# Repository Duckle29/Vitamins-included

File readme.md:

View this project on [CADLAB.io](https://cadlab.io/project/1862).   
View the [iBOM](https://duckle29.github.io/Vitamins-included/ibom.html)

# Vitamins Included

This repository contains all files necesarry to make the Let's split keyboard variant "Vitamins included"

Files are not guarranteed to be in sync outside of tagged releases. They aren't on releases either, but they should be ;)

The kit for these PCBs are sold at [Novelkeys](https://novelkeys.xyz), 
the firmware for the keyboard is [QMK](https://github.com/qmk/qmk_firmware/tree/master/keyboards/vitamins_included)

To edit these, you need kicad 5 or later. Missing footprints can be found [here](https://github.com/Duckle29/kicad-footprints), on seperate branches, but should be included in KiCAD libraries eventually. You can check for open pull-requests by me on the upstream repo to see the status on those.

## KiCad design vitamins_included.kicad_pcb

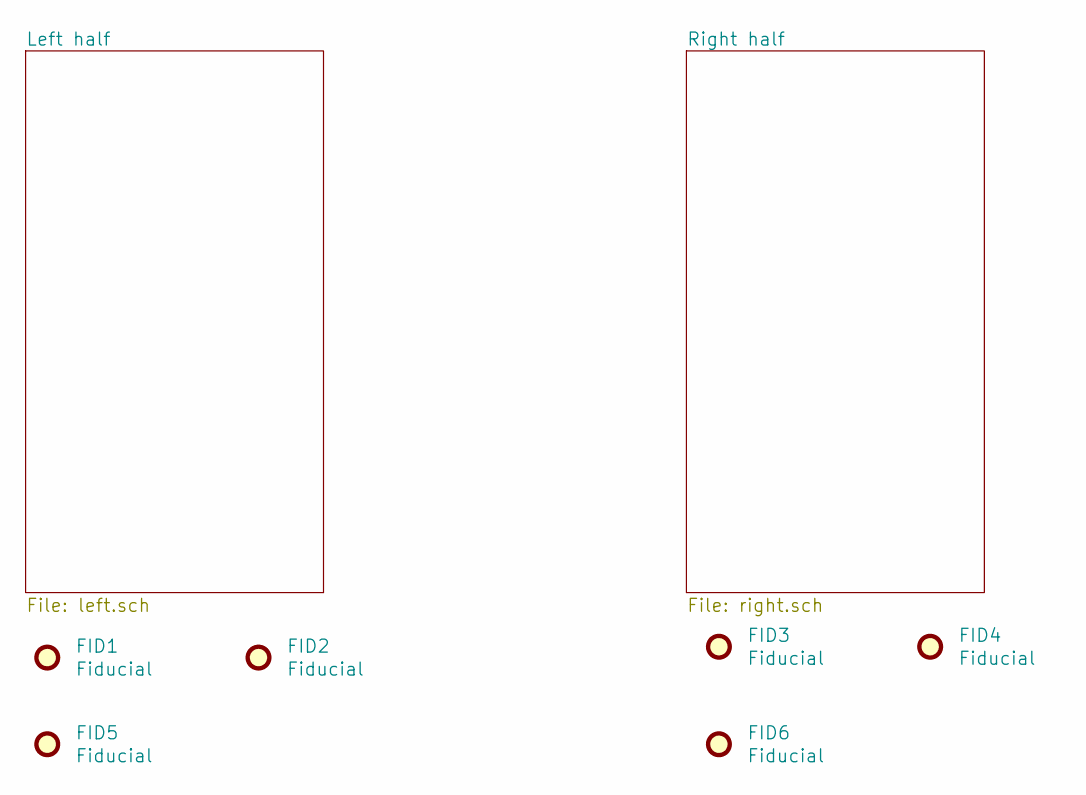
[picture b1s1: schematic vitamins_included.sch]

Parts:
FID1, FID2, FID3, FID4, FID5, FID6: Fiducial; Fiducial_1mm_Dia_2mm_Outer

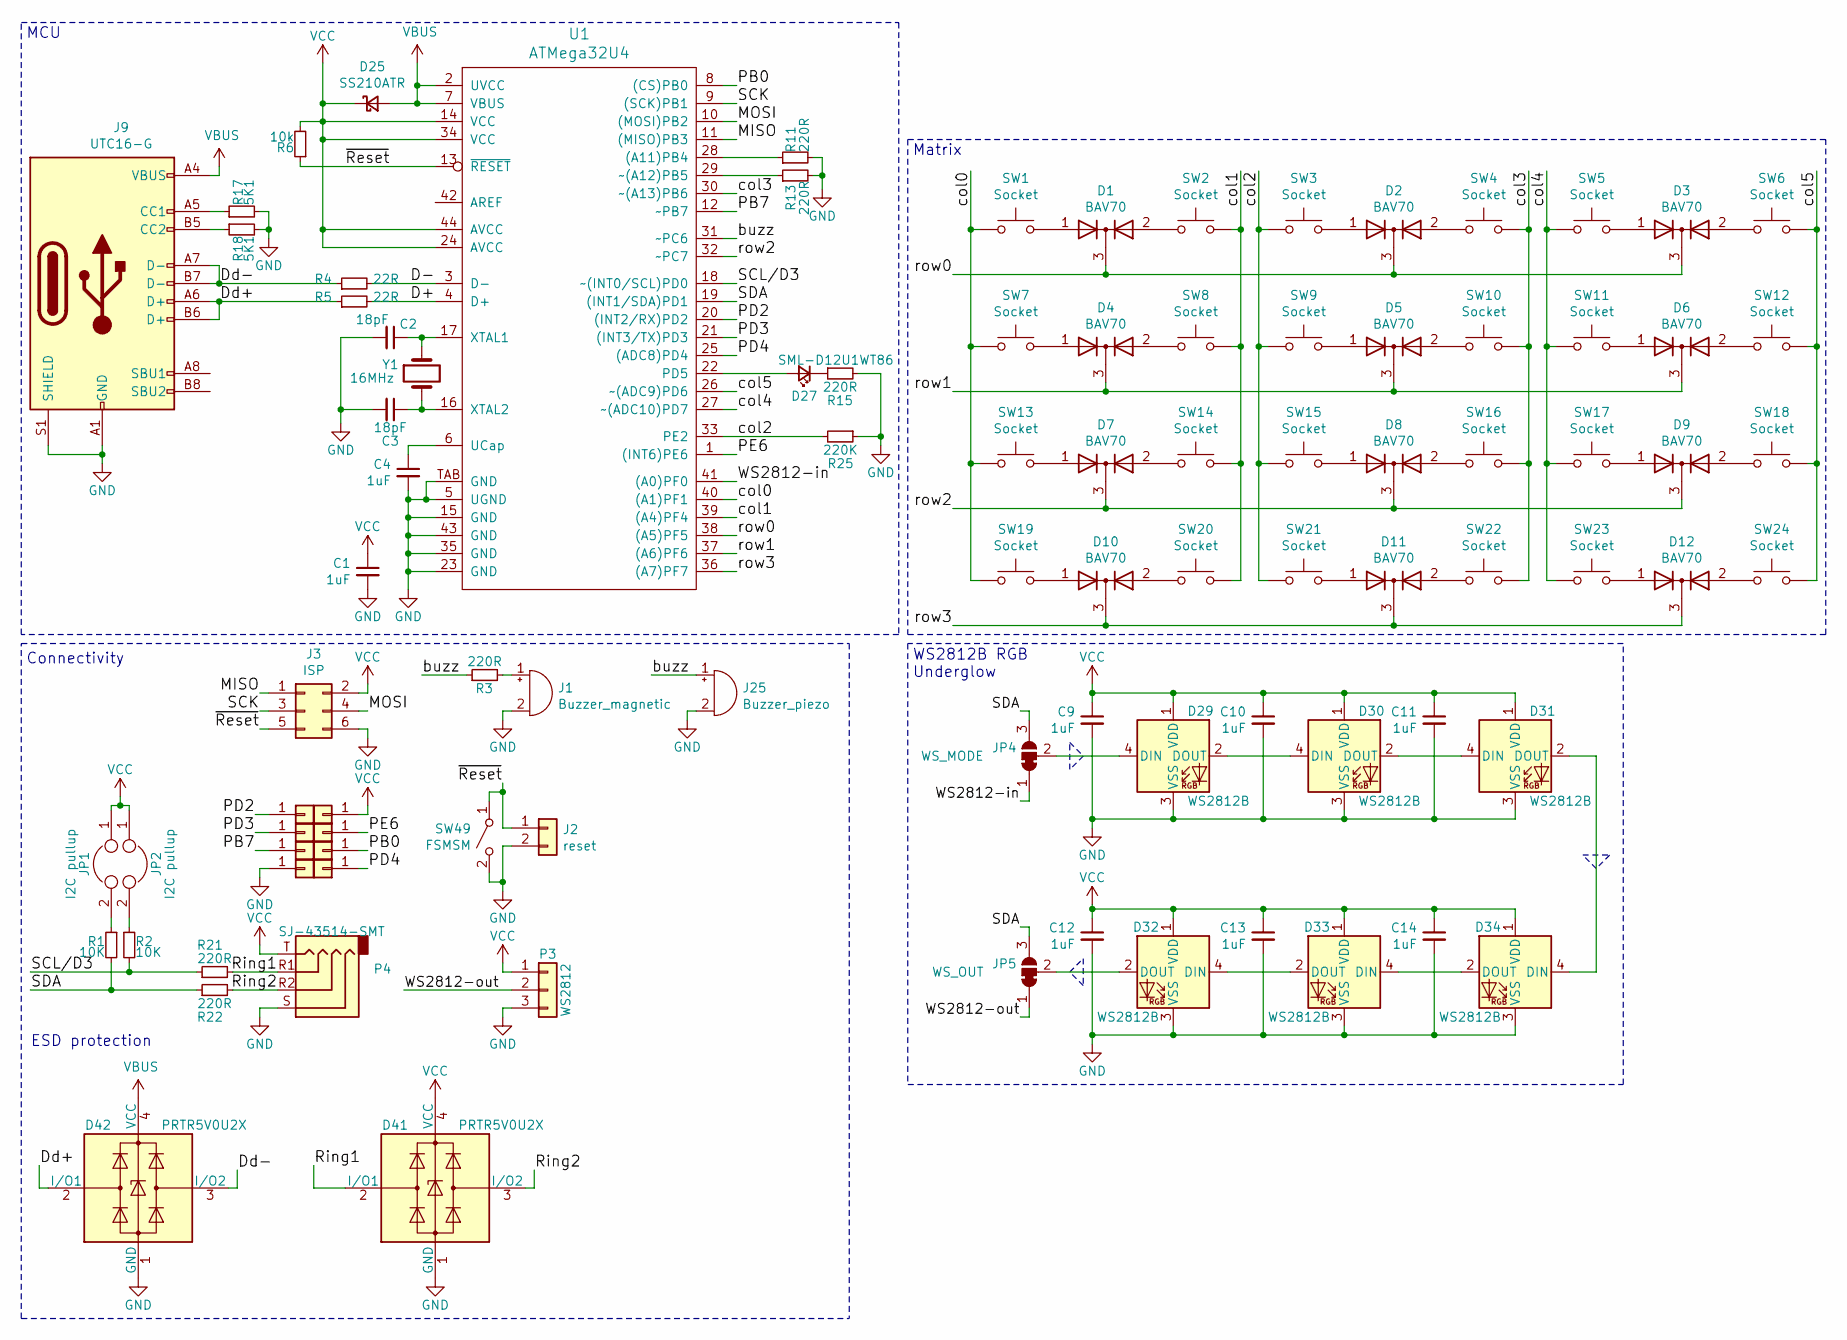
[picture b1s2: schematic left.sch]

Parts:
C1, C4, C9, C10, C11, C12, C13, C14: 1uF; C_0603_1608Metric
C2, C3: 18pF; C_0603_1608Metric
D1, D2, D3, D4, D5, D6, D7, D8, D9, D10, D11, D12: BAV70; SOT-23
D25: SS210ATR; D_SMA
D27: SML-D12U1WT86; LED_0603_1608Metric_Castellated
D29, D30, D31, D32, D33, D34: WS2812B; LED_WS2812B_PLCC4_5.0x5.0mm_P3.2mm
D41, D42: PRTR5V0U2X; SOT-143
J1: Buzzer_magnetic; Buzzer_12x9.5RM7.6
J2: reset; PinHeader_1x02_P2.54mm_Vertical
J3: ISP; Tag-Connect_TC2030-IDC-NL_2x03_P1.27mm_Vertical
J7, J11, J12, J13, J14, J15, J16, J17: Conn_01x01; TestPoint_Pad_D1.5mm
J9: UTC16-G; USB_C_Receptacle_Palconn_UTC16-G
J25: Buzzer_piezo; Buzzer_Mallory_AST1109MLTRQ
JP1, JP2: I2C pullup; Solder-jumper-NO
JP4: WS_MODE; SolderJumper-3_P1.3mm_Bridged12_RoundedPad1.0x1.5mm
JP5: WS_OUT; SolderJumper-3_P1.3mm_Bridged12_RoundedPad1.0x1.5mm
P3: WS2812; SMD_PAD_1x03_Pitch2.54mm
P4: SJ-43514-SMT; SJ-4351X-SMT
R1, R2: 10K; R_0603_1608Metric
R3, R11, R13, R15, R21, R22: 220R; R_0603_1608Metric
R4, R5: 22R; R_0603_1608Metric
R6: 10k; R_0603_1608Metric
R17, R18: 5K1; R_0603_1608Metric
R25: 220K; R_0603_1608Metric
SW1, SW2, SW3, SW4, SW5, SW6, SW7, SW8, SW9, SW10, SW11, SW12, SW13, SW14, SW15, SW16, SW17, SW18, SW19, SW20, SW21, SW22, SW23, SW24: Socket; Kailh-socket
SW49: FSMSM; SW_SPST_FSMSM
U1: ATMega32U4; QFN44G-0.5-7X7MM
Y1: 16MHz; Crystal_SMD_Abracon_ABM3-2pin_5.0x3.2mm

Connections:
/Left half/D+: R5.2, U1.4 (D+)
/Left half/D-: R4.2, U1.3 (D-)
/Left half/Dd+: D42.2 (I/O1), J9.A6 (D+), J9.B6 (D+), R5.1
/Left half/Dd-: D42.3 (I/O2), J9.A7 (D-), J9.B7 (D-), R4.1
/Left half/MISO: J3.1, U1.11 ((MISO)PB3); also elsewhere on the board
/Left half/MOSI: J3.4, U1.10 ((MOSI)PB2); also elsewhere on the board
/Left half/PB0: J15.1, U1.8 ((CS)PB0)
/Left half/PB7: J14.1, U1.12 (~~PB7)
/Left half/PD2: J12.1, U1.20 ((INT2/RX)PD2)
/Left half/PD3: J7.1, U1.21 ((INT3/TX)PD3)
/Left half/PD4: J11.1, U1.25 ((ADC8)PD4)
/Left half/PE6: J13.1, U1.1 ((INT6)PE6)
/Left half/Ring1: D41.2 (I/O1), P4.R1, R21.2
/Left half/Ring2: D41.3 (I/O2), P4.R2, R22.2
/Left half/SCK: J3.3, U1.9 ((SCK)PB1); also elsewhere on the board
/Left half/SCL/D3: R2.2, R21.1, U1.18 (~~(INT0/SCL)PD0)
/Left half/SDA: JP4.3 (B), JP5.3 (B), R1.2, R22.1, U1.19 ((INT1/SDA)PD1)
/Left half/WS2812-in: JP4.1 (A), U1.41 ((A0)PF0)
/Left half/WS2812-out: JP5.1 (A), P3.2
/Left half/buzz: J25.1 (-), R3.1, U1.31 (~~PC6)
/Left half/col0: SW1.1, SW7.1, SW13.1, SW19.1, U1.40 ((A1)PF1)
/Left half/col1: SW2.2, SW8.2, SW14.2, SW20.2, U1.39 ((A4)PF4)
/Left half/col2: R25.2, SW3.1, SW9.1, SW15.1, SW21.1, U1.33 (PE2)
/Left half/col3: SW4.2, SW10.2, SW16.2, SW22.2, U1.30 (~~(A13)PB6)
/Left half/col4: SW5.1, SW11.1, SW17.1, SW23.1, U1.27 (~~(ADC10)PD7)
/Left half/col5: SW6.2, SW12.2, SW18.2, SW24.2, U1.26 (~~(ADC9)PD6); also elsewhere on the board
/Left half/row0: D1.3 (K), D2.3 (K), D3.3 (K), U1.38 ((A5)PF5)
/Left half/row1: D4.3 (K), D5.3 (K), D6.3 (K), U1.37 ((A6)PF6)
/Left half/row2: D7.3 (K), D8.3 (K), D9.3 (K), U1.32 (~~PC7)
/Left half/row3: D10.3 (K), D11.3 (K), D12.3 (K), U1.36 ((A7)PF7)
/Left half/~Reset: J2.1, J3.5, R6.1, SW49.1 (A), U1.13 (~RESET~)
unnamed: C2.1, U1.17 (XTAL1), Y1.1
unnamed: C3.1, U1.16 (XTAL2), Y1.2
unnamed: C4.1, U1.6 (UCap)
unnamed: D1.1 (A), SW1.2
unnamed: D1.2 (A), SW2.1
unnamed: D2.1 (A), SW3.2
unnamed: D2.2 (A), SW4.1
unnamed: D3.1 (A), SW5.2
unnamed: D3.2 (A), SW6.1
unnamed: D4.1 (A), SW7.2
unnamed: D4.2 (A), SW8.1
unnamed: D5.1 (A), SW9.2
unnamed: D5.2 (A), SW10.1
unnamed: D6.1 (A), SW11.2
unnamed: D6.2 (A), SW12.1
unnamed: D7.1 (A), SW13.2
unnamed: D7.2 (A), SW14.1
unnamed: D8.1 (A), SW15.2
unnamed: D8.2 (A), SW16.1
unnamed: D9.1 (A), SW17.2
unnamed: D9.2 (A), SW18.1
unnamed: D10.1 (A), SW19.2
unnamed: D10.2 (A), SW20.1
unnamed: D11.1 (A), SW21.2
unnamed: D11.2 (A), SW22.1
unnamed: D12.1 (A), SW23.2
unnamed 90: D12.2 (A), SW24.1; also elsewhere on the board
unnamed: D27.1 (K), R15.1
unnamed: D27.2 (A), U1.22 (PD5)
unnamed: D29.2 (DOUT), D30.4 (DIN)
unnamed: D29.4 (DIN), JP4.2 (C)
unnamed: D30.2 (DOUT), D31.4 (DIN)
unnamed: D31.2 (DOUT), D34.4 (DIN)
unnamed: D32.2 (DOUT), JP5.2 (C)
unnamed: D32.4 (DIN), D33.2 (DOUT)
unnamed: D33.4 (DIN), D34.2 (DOUT)
unnamed: J1.1 (-), R3.2
unnamed: J9.A5 (CC1), R17.1
unnamed: J9.B5 (CC2), R18.1
unnamed: JP1.2, R1.1
unnamed: JP2.2, R2.1
unnamed: R11.1, U1.28 ((A11)PB4)
unnamed: R13.1, U1.29 (~~(A12)PB5)
VBUS: D25.2 (A), D42.4 (VCC), J9.A4 (VBUS), J9.A9 (VBUS), J9.B4 (VBUS), J9.B9 (VBUS), U1.2 (UVCC), U1.7 (VBUS); also elsewhere on the board
VCC: C1.1, C9.1, C10.1, C11.1, C12.1, C13.1, C14.1, D25.1 (K), D29.1 (VDD), D30.1 (VDD), D31.1 (VDD), D32.1 (VDD), D33.1 (VDD), D34.1 (VDD), D41.4 (VCC), J3.2, J17.1, JP1.1, JP2.1, P3.1, P4.T, R6.2, U1.14 (VCC), U1.24 (AVCC), U1.34 (VCC), U1.44 (AVCC); also elsewhere on the board

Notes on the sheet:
MCU
WS2812B RGB Underglow
Matrix
Connectivity
ESD protection

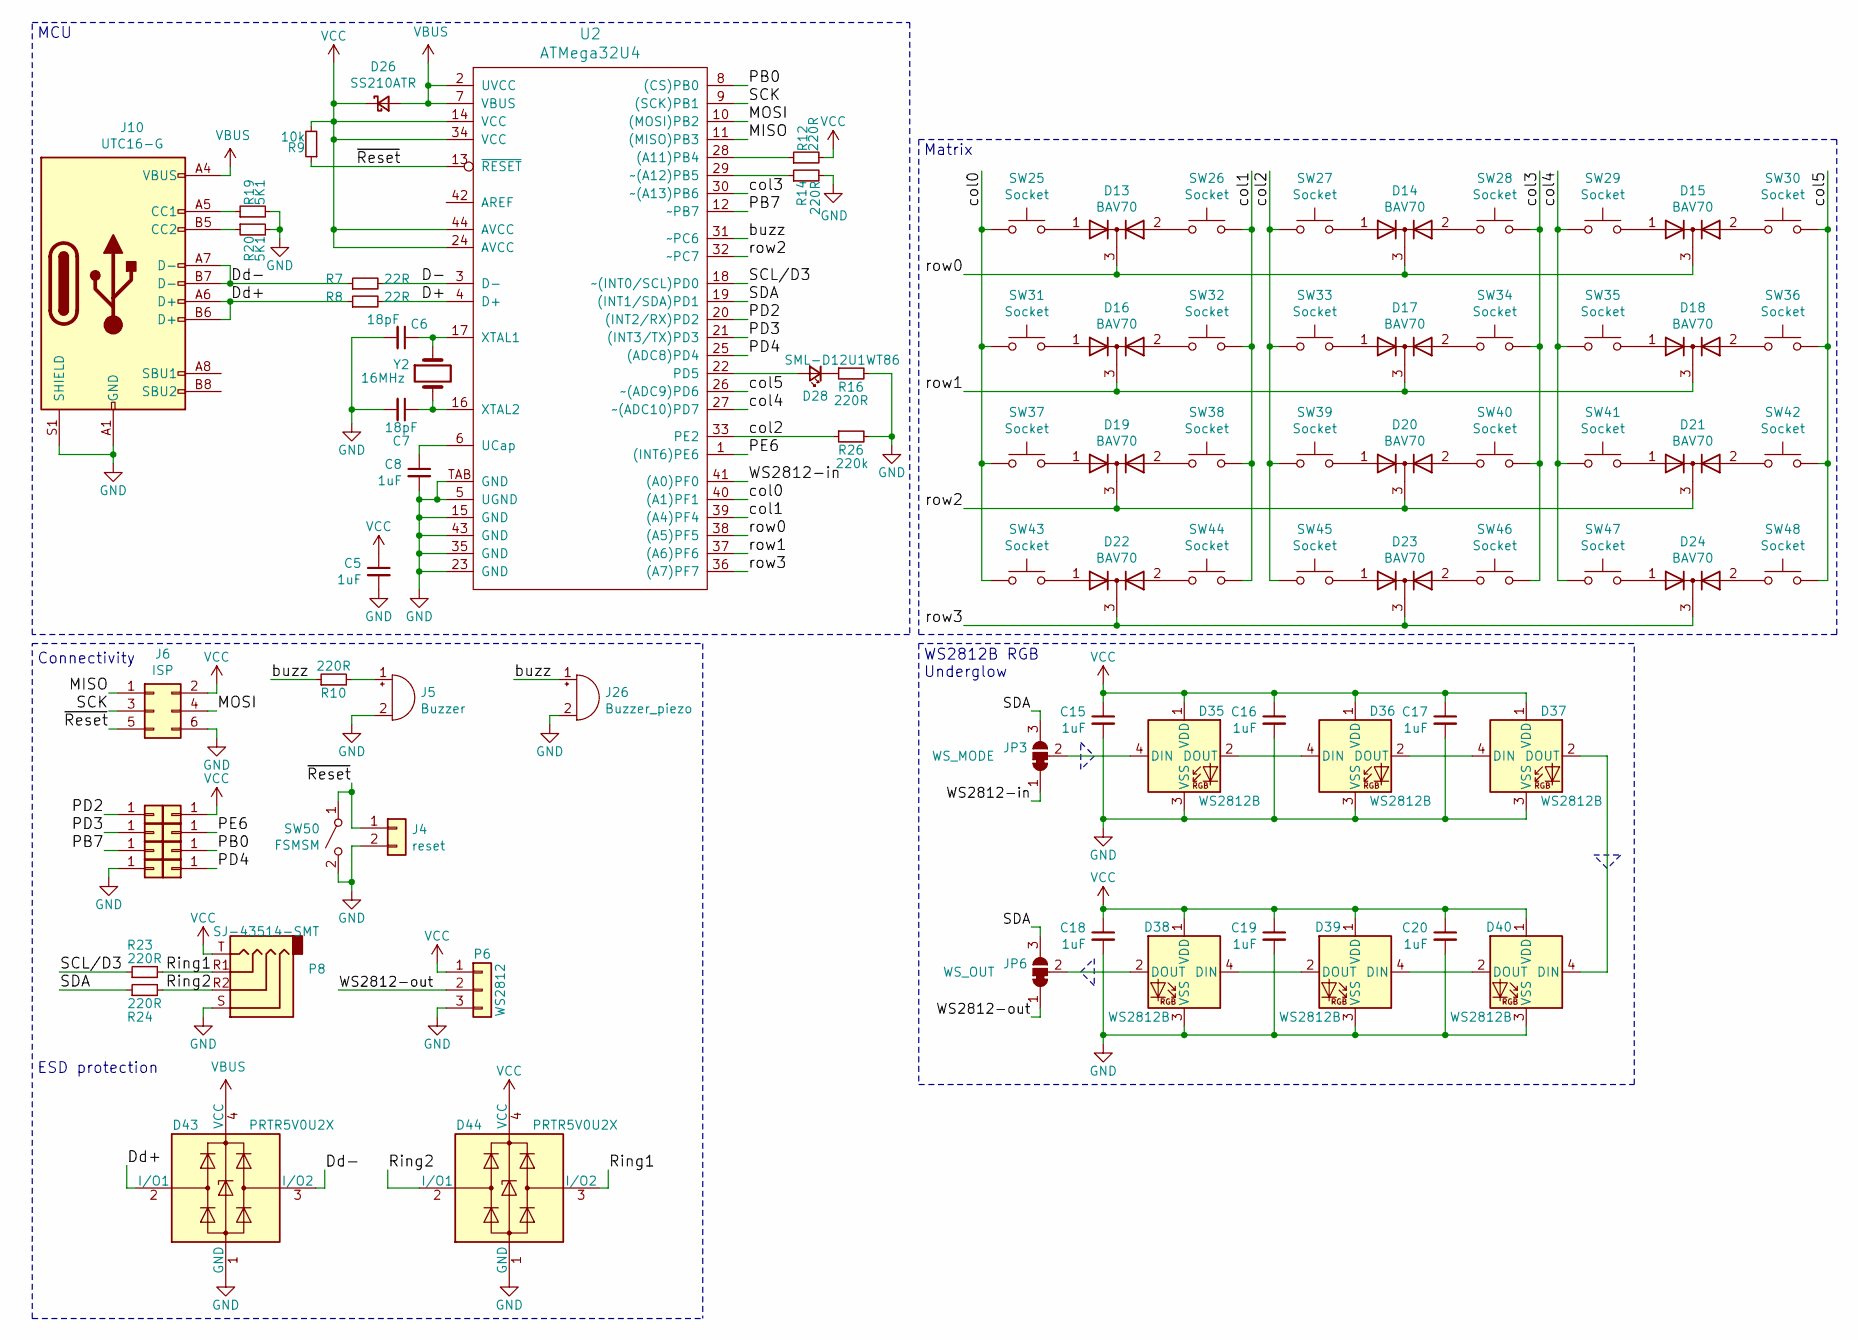
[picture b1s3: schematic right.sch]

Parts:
C5, C8, C15, C16, C17, C18, C19, C20: 1uF; C_0603_1608Metric
C6, C7: 18pF; C_0603_1608Metric
D13, D14, D15, D16, D17, D18, D19, D20, D21, D22, D23, D24: BAV70; SOT-23
D26: SS210ATR; D_SMA
D28: SML-D12U1WT86; LED_0603_1608Metric_Castellated
D35, D36, D37, D38, D39, D40: WS2812B; LED_WS2812B_PLCC4_5.0x5.0mm_P3.2mm
D43, D44: PRTR5V0U2X; SOT-143
J4: reset; PinHeader_1x02_P2.54mm_Vertical
J5: Buzzer; Buzzer_12x9.5RM7.6
J6: ISP; Tag-Connect_TC2030-IDC-NL_2x03_P1.27mm_Vertical
J8, J18, J19, J20, J21, J22, J23, J24: Conn_01x01; TestPoint_Pad_D1.5mm
J10: UTC16-G; USB_C_Receptacle_Palconn_UTC16-G
J26: Buzzer_piezo; Buzzer_Mallory_AST1109MLTRQ
JP3: WS_MODE; SolderJumper-3_P1.3mm_Bridged12_RoundedPad1.0x1.5mm
JP6: WS_OUT; SolderJumper-3_P1.3mm_Bridged12_RoundedPad1.0x1.5mm
P6: WS2812; SMD_PAD_1x03_Pitch2.54mm
P8: SJ-43514-SMT; SJ-4351X-SMT
R7, R8: 22R; R_0603_1608Metric
R9: 10k; R_0603_1608Metric
R10, R12, R14, R16, R23, R24: 220R; R_0603_1608Metric
R19, R20: 5K1; R_0603_1608Metric
R26: 220k; R_0603_1608Metric
SW25, SW26, SW27, SW28, SW29, SW30, SW31, SW32, SW33, SW34, SW35, SW36, SW37, SW38, SW39, SW40, SW41, SW42, SW43, SW44, SW45, SW46, SW47, SW48: Socket; Kailh-socket
SW50: FSMSM; SW_SPST_FSMSM
U2: ATMega32U4; QFN44G-0.5-7X7MM
Y2: 16MHz; Crystal_SMD_Abracon_ABM3-2pin_5.0x3.2mm

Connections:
/Right half/D+: R8.2, U2.4 (D+)
/Right half/D-: R7.2, U2.3 (D-)
/Right half/Dd+: D43.2 (I/O1), J10.A6 (D+), J10.B6 (D+), R8.1
/Right half/Dd-: D43.3 (I/O2), J10.A7 (D-), J10.B7 (D-), R7.1
/Right half/MISO: J6.1, U2.11 ((MISO)PB3); also elsewhere on the board
/Right half/MOSI: J6.4, U2.10 ((MOSI)PB2); also elsewhere on the board
/Right half/PB0: J22.1, U2.8 ((CS)PB0)
/Right half/PB7: J21.1, U2.12 (~~PB7)
/Right half/PD2: J8.1, U2.20 ((INT2/RX)PD2)
/Right half/PD3: J19.1, U2.21 ((INT3/TX)PD3)
/Right half/PD4: J24.1, U2.25 ((ADC8)PD4)
/Right half/PE6: J20.1, U2.1 ((INT6)PE6)
/Right half/Ring1: D44.3 (I/O2), P8.R1, R23.2
/Right half/Ring2: D44.2 (I/O1), P8.R2, R24.2
/Right half/SCL/D3: R23.1, U2.18 (~~(INT0/SCL)PD0)
/Right half/SDA: JP3.3 (B), JP6.3 (B), R24.1, U2.19 ((INT1/SDA)PD1)
/Right half/WS2812-in: JP3.1 (A), U2.41 ((A0)PF0)
/Right half/WS2812-out: JP6.1 (A), P6.2
/Right half/buzz: J26.1 (-), R10.1, U2.31 (~~PC6)
/Right half/col0: SW25.1, SW31.1, SW37.1, SW43.1, U2.40 ((A1)PF1); also elsewhere on the board
/Right half/col1: SW26.2, SW32.2, SW38.2, SW44.2, U2.39 ((A4)PF4)
/Right half/col2: R26.1, SW27.1, SW33.1, SW39.1, SW45.1, U2.33 (PE2)
/Right half/col3: SW28.2, SW34.2, SW40.2, SW46.2, U2.30 (~~(A13)PB6)
/Right half/col4: SW29.1, SW35.1, SW41.1, SW47.1, U2.27 (~~(ADC10)PD7)
/Right half/col5: SW30.2, SW36.2, SW42.2, SW48.2, U2.26 (~~(ADC9)PD6)
/Right half/row0: D13.3 (K), D14.3 (K), D15.3 (K), U2.38 ((A5)PF5)
/Right half/row1: D16.3 (K), D17.3 (K), D18.3 (K), U2.37 ((A6)PF6)
/Right half/row2: D19.3 (K), D20.3 (K), D21.3 (K), U2.32 (~~PC7)
/Right half/row3: D22.3 (K), D23.3 (K), D24.3 (K), U2.36 ((A7)PF7)
/Right half/~Reset: J4.1, J6.5, R9.1, SW50.1 (A), U2.13 (~RESET~)
unnamed: C6.1, U2.17 (XTAL1), Y2.1
unnamed: C7.1, U2.16 (XTAL2), Y2.2
unnamed: C8.1, U2.6 (UCap)
unnamed: D13.1 (A), SW25.2
unnamed: D13.2 (A), SW26.1
unnamed: D14.1 (A), SW27.2
unnamed: D14.2 (A), SW28.1
unnamed: D15.1 (A), SW29.2
unnamed: D15.2 (A), SW30.1
unnamed: D16.1 (A), SW31.2
unnamed: D16.2 (A), SW32.1
unnamed: D17.1 (A), SW33.2
unnamed: D17.2 (A), SW34.1
unnamed: D18.1 (A), SW35.2
unnamed: D18.2 (A), SW36.1
unnamed: D19.1 (A), SW37.2
unnamed: D19.2 (A), SW38.1
unnamed: D20.1 (A), SW39.2
unnamed: D20.2 (A), SW40.1
unnamed: D21.1 (A), SW41.2
unnamed: D21.2 (A), SW42.1
unnamed 109: D22.1 (A), SW43.2; also elsewhere on the board
unnamed: D22.2 (A), SW44.1
unnamed: D23.1 (A), SW45.2
unnamed: D23.2 (A), SW46.1
unnamed: D24.1 (A), SW47.2
unnamed: D24.2 (A), SW48.1
unnamed: D28.1 (K), R16.1
unnamed: D28.2 (A), U2.22 (PD5)
unnamed: D35.2 (DOUT), D36.4 (DIN)
unnamed: D35.4 (DIN), JP3.2 (C)
unnamed: D36.2 (DOUT), D37.4 (DIN)
unnamed: D37.2 (DOUT), D40.4 (DIN)
unnamed: D38.2 (DOUT), JP6.2 (C)
unnamed: D38.4 (DIN), D39.2 (DOUT)
unnamed: D39.4 (DIN), D40.2 (DOUT)
unnamed: J5.1 (-), R10.2
unnamed: J10.A5 (CC1), R19.1
unnamed: J10.B5 (CC2), R20.1
unnamed: R12.1, U2.28 ((A11)PB4)
unnamed: R14.1, U2.29 (~~(A12)PB5)
VBUS: D26.2 (A), D43.4 (VCC), J10.A4 (VBUS), J10.A9 (VBUS), J10.B4 (VBUS), J10.B9 (VBUS), U2.2 (UVCC), U2.7 (VBUS); also elsewhere on the board
VCC: C5.1, C15.1, C16.1, C17.1, C18.1, C19.1, C20.1, D26.1 (K), D35.1 (VDD), D36.1 (VDD), D37.1 (VDD), D38.1 (VDD), D39.1 (VDD), D40.1 (VDD), D44.4 (VCC), J6.2, J18.1, P6.1, P8.T, R9.2, R12.2, U2.14 (VCC), U2.24 (AVCC), U2.34 (VCC), U2.44 (AVCC); also elsewhere on the board

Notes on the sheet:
MCU
WS2812B RGB Underglow
Matrix
Connectivity
ESD protection

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
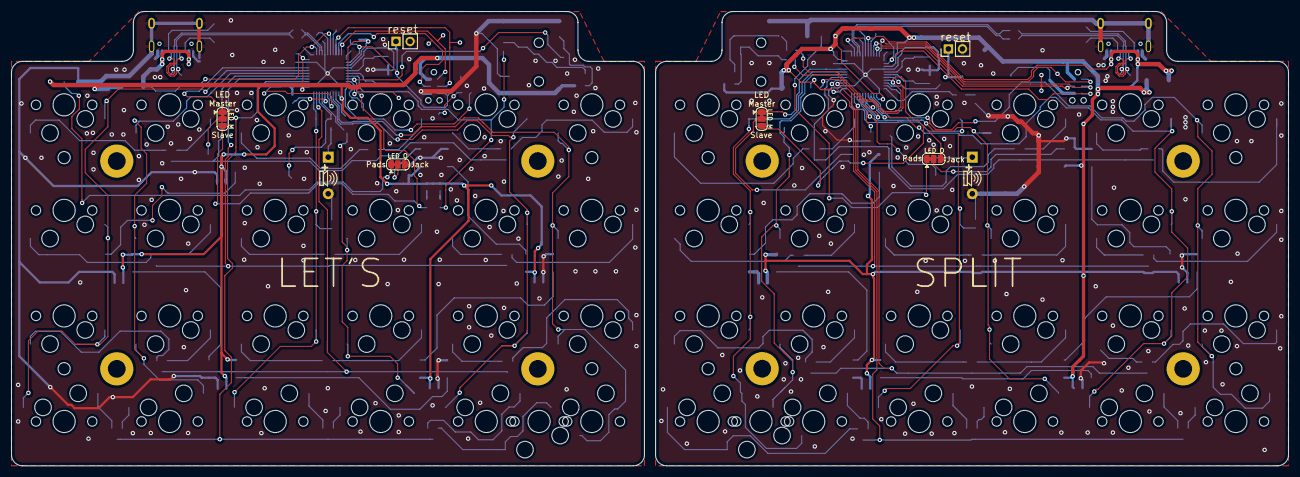
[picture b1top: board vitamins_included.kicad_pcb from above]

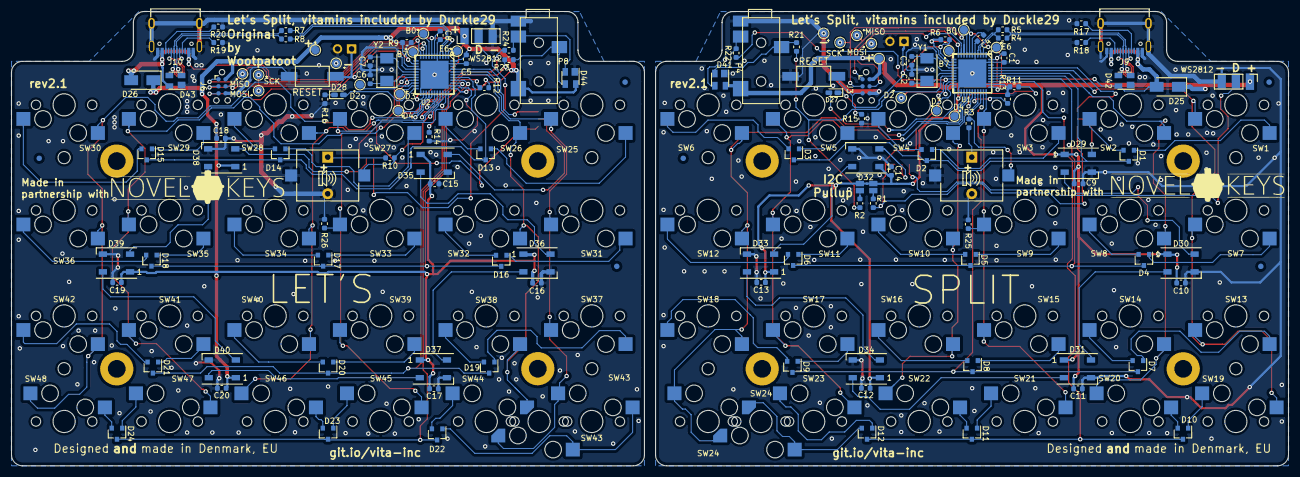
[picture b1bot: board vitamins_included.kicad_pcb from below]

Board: 2 copper layers, 230.5 x 82.0 mm, 194 parts (188 on the bottom side), 149 nets.

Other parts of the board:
J16#2, J16#3, J16#4, J16#5, J16#6, J16#7: Conn_01x01; TestPoint_Pad_D1.5mm
SW24#2, SW43#2: Socket; Kailh-socket

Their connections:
/Left half/MISO: J16#6.1; also elsewhere on the board
/Left half/MOSI: J16#5.1; also elsewhere on the board
/Left half/SCK: J16#4.1; also elsewhere on the board
/Left half/col5: SW24#2.2; also elsewhere on the board
/Right half/MISO: J16#2.1; also elsewhere on the board
/Right half/MOSI: J16#3.1; also elsewhere on the board
/Right half/col0: SW43#2.1; also elsewhere on the board
unnamed 90: SW24#2.1; also elsewhere on the board
unnamed 109: SW43#2.2; also elsewhere on the board

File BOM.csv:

Id,Designator,Package,Quantity,Designation,Supplier and ref
1,"P5,P2",USB-Mini-B-SMD,2,UJ2-MBH-1-SMT,
2,"D21,D16,D23,D14,D20,D22,D19,D24,D17,D15,D13,D18,D2,D8,D6,D12,D3,D7,D10,D4,D9,D11,D5,D1",SOT-23,24,BAV70,
3,"R7,R8,R5,R4",R_0603,4,22R,
4,"SW40,SW36,SW41,SW43,SW44,SW42,SW45,SW43,SW35,SW28,SW34,SW48,SW47,SW33,SW39,SW32,SW26,SW29,SW46,SW30,SW38,SW27,SW31,SW25,SW37,SW19,SW12,SW21,SW23,SW24,SW24,SW6,SW15,SW4,SW5,SW13,SW20,SW1,SW22,SW16,SW17,SW8,SW10,SW11,SW7,SW9,SW18,SW2,SW14,SW3",Kailh-socket,50,Socket,
5,"Y2,Y1",Crystal_SMD_Abracon_ABM3-2pin_5.0x3.2mm,2,16MHz,
6,"P8,P4",SJ-4351X-SMT,2,SJ-43514-SMT,
7,"C6,C7,C2,C3",C_0603,4,18pF,
8,"C5,C8,C1,C4",C_0603,4,1uF,
9,"U2,U1",QFN44G-0.5-7X7MM,2,ATMega32U4,
10,"R10,R3",R_0603,2,200R,
11,"R9,R1,R2,R6",R_0603,4,4k7,
12,"J5,J1",Buzzer_12x9.5RM7.6,2,Speaker,
13,,,,,
14,,,,,
15,,,,,
16,,,,,
17,,,,,
18,,,,,
19,,,,,
20,,,,,

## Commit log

2018-07-19 Initial commit, moving project to it's own repo
2018-07-19 Updated renders
2018-07-19 shuffling names to refresh images on github
2018-07-19 renamed files, and generated xy files
2018-07-19 Added BOM and 3D file
2018-07-19 Added resistors to allow MCU to determin which half it is on
2018-07-20 Changed to USB-C connector
2018-07-22 Added resistors to allow the firmware to determine version
2018-07-22 changed to rounded passive footprints
2018-07-22 Exported new 3d files
2018-07-22 Added Schematic pdf
2018-07-22 Added a Dimensions PDF for case-makers
2018-07-22 spelling mistake
2018-07-27 Switched to connectors
2018-07-27 Fixed 3Dmodels for sockets.Exported new renders
2018-07-27 Exported new fabriation files
2018-07-27 Ran DRC, fixed things
2018-07-27 file-jiggling to refresh readme images
2018-07-27 Organized silkscreen
2018-07-27 Jiggled filenames to update readme renders
2018-07-27 More jiggle
2018-07-27 moved image back. oops
2018-07-27 Git why is my image upside down :(
2018-07-27 You can do it github
2018-07-27 Renamed image to hopefully update it
2018-07-30 Added reset button, led, 3D models
2018-07-30 Re-rendered images
2018-07-30 Jiggling images to force re-render
2018-07-30 More jiggling requried
2018-07-30 jiggling
2018-07-31 Rev2 production run
2018-08-03 Fixed schematic PDF
2018-09-03 Broke something. who knows
2018-09-03 fixed readme
2018-09-21 Delfi
2018-09-21 Production state
2018-11-27 Added WS2812B leds to one half
2018-11-27 started work on second half
2019-01-31 Added ws2812 LEDs
2019-01-31 Updated BOM
2019-01-31 Update images in readme
2019-01-31 Removed ? from image paths
2019-01-31 Added zipped gerbers
2019-02-21 Exported fabrication outputs for qoute
2019-02-27 Fixed rotated LEDs, added config jumpers
2019-02-27 Exported new fabrication outputs
2019-03-03 Added MPN to DFU LED
2019-03-17 Fixed USB-C footprint
2019-03-18 Updated gerbers
2019-03-27 Added X2 gerbers and updated BOM
2019-06-11 Backlink to CADLAB.io has been added.
2019-07-04 Added 5k1 CC resistors
2019-07-04 Genereated new gerbers
2019-07-04 Added R17-20 to BOM
2019-07-06 Switched to main library 3D model
2019-07-06 Removed local 3d model
2019-07-26 Pre-cleanup
2019-07-26 Fixed symbols to not rely on rescue
2019-08-15 Create LICENSE
2019-10-07 Added footprint for AST1109MLTRQ buzzer
2019-10-07 Modified reset switch footprint for better manufacturing, and added updated gerbers
2019-10-07 Added ESD protection to connectors
2019-10-07 Added series resistors on TRRS
2019-10-07 Update LICENSE
2020-09-30 Added PE2 pull-down for dfu
2020-09-30 saved schematics
2020-09-30 Updated I2C pull-up values
    Updated the values to ensure the effect of the newly added series resistors don't cause the low level to exceed chip specifications for i2c potentially leading to communication issues if using i2c
2020-09-30 Removed outdated gerbers and BOM to avoid confusion
2020-09-30 Added updated gerbers, BOM and position files
2020-10-01 Added iBOM
2020-10-01 Added iBOM to readme
2020-10-01 Rename index.html to ibom.html
2020-10-02 Update values in pcb and ibom
2020-11-16 Added solder pads for SPI
2020-11-16 Exported gerbers
2020-11-16 Added gerbers
2020-12-07 Fixed MISO solder-pad labels
2020-12-07 Fixed sck-gnd short, fixed missing vbus trace
